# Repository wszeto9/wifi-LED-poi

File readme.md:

# WiFi-LED-Poi
USB-C Rechargable, WiFi Capable Glow Poi

<h2> Features:</h2>
<ul>
<li>ESP-32 MCU capable of WiFi-communication and syncronization of lights with music</li>
<li>Rechargable battery with a battery life of 3.5-5 hours</li>
<li>Programmable over USB-C</li>
<li>Charging over USB-C</li>
<li>0.47F Supercapacitor capable of nefarious discharge acts</li>
<li>Onboard accelerometer and microphone</li>
</ul>

PCB Bottom

PCB Top

PCBA

Glow Poi assembled with shell and battery

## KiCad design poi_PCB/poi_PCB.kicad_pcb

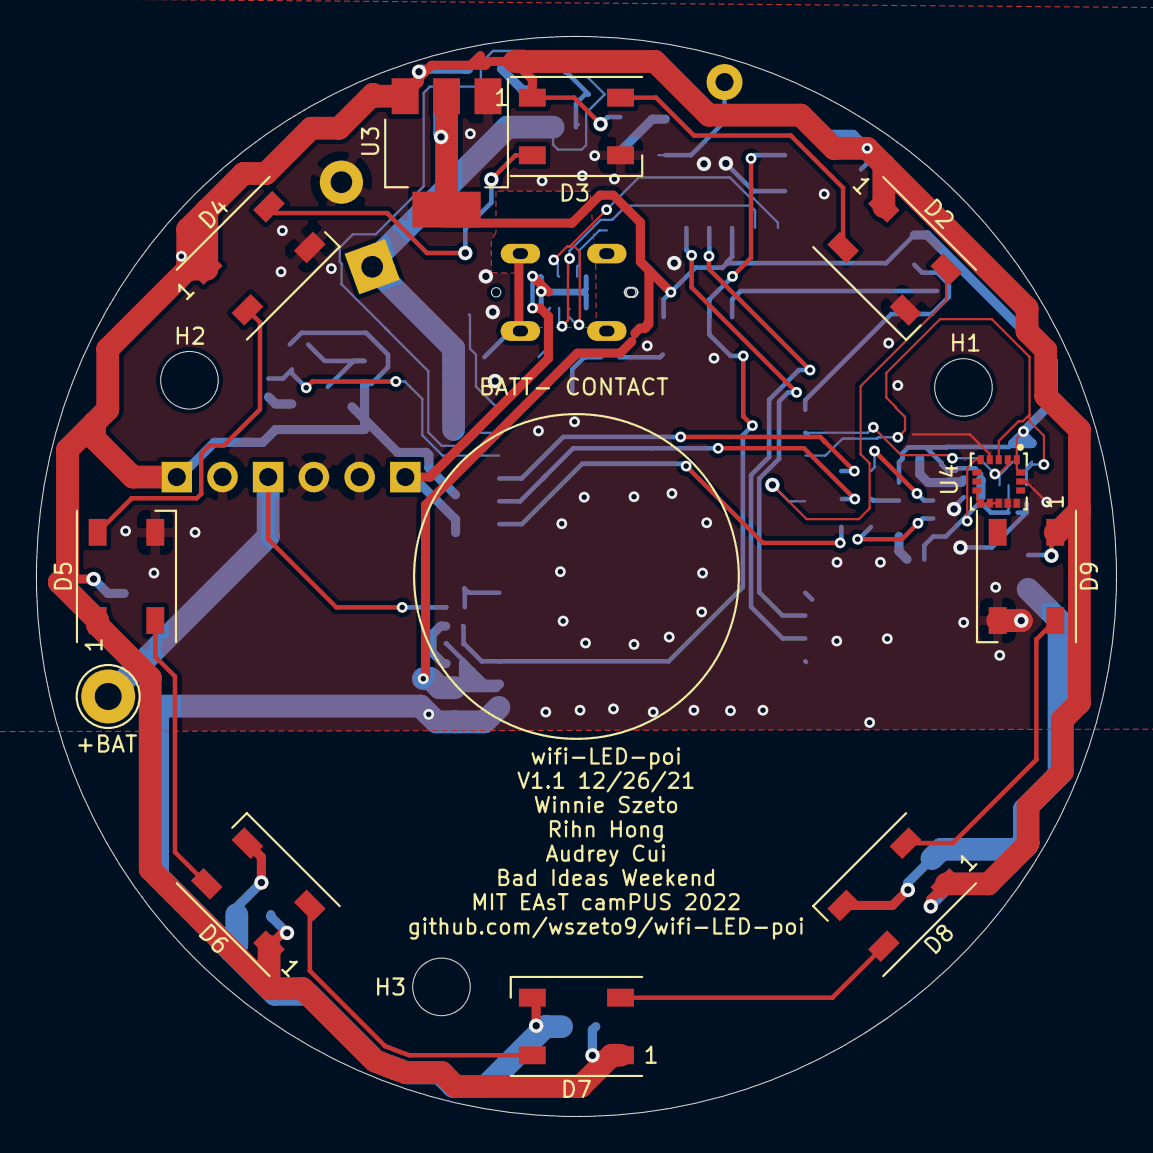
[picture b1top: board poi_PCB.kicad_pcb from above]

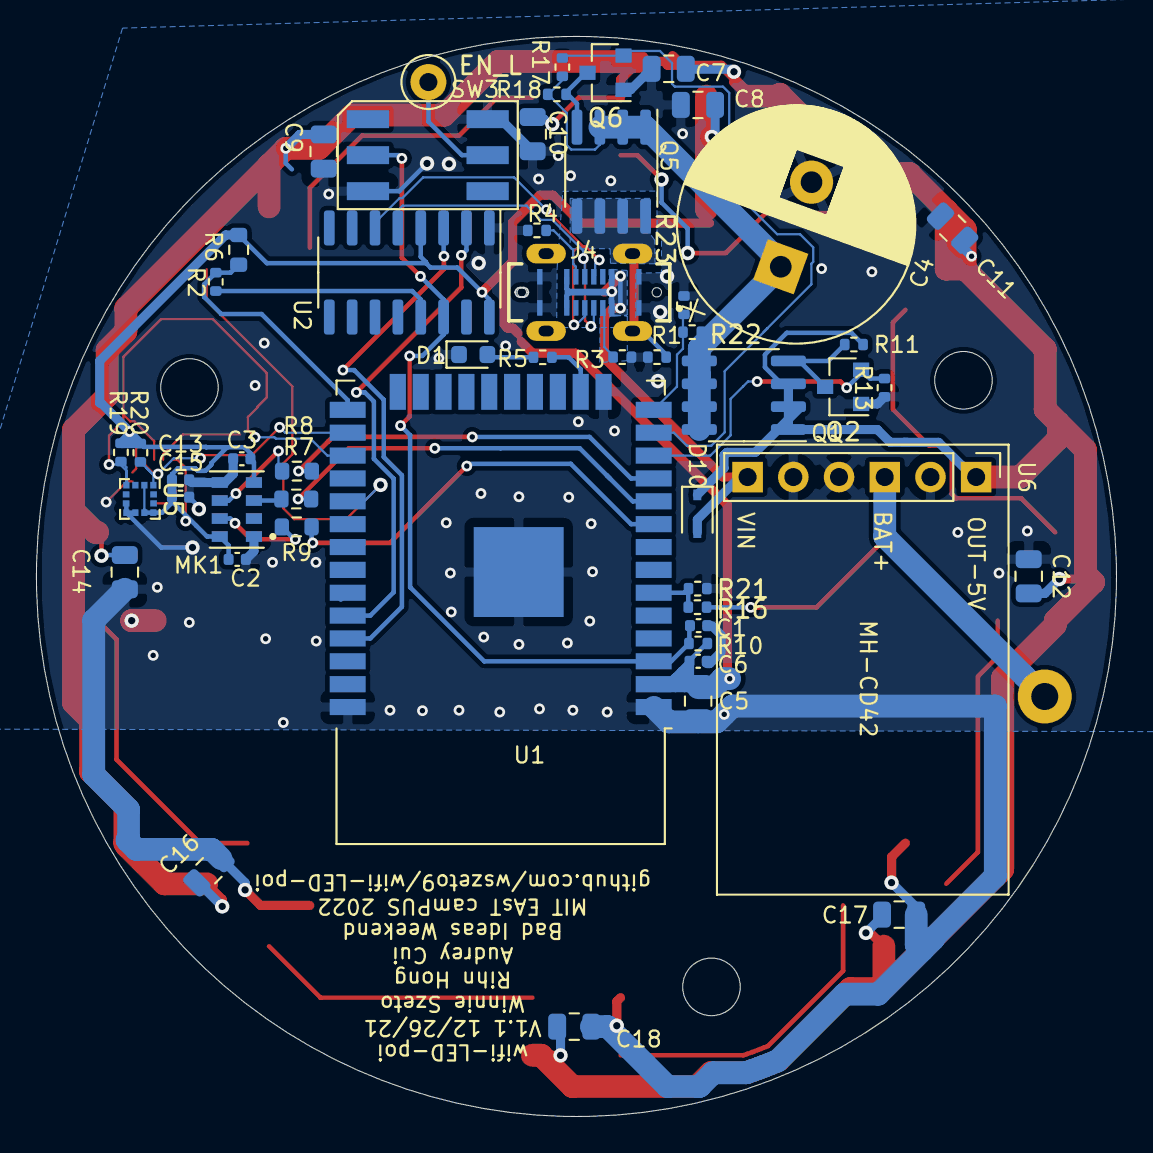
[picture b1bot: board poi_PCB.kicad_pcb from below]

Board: 2 copper layers, 60.0 x 60.0 mm, 66 parts (52 on the bottom side), 41 nets.

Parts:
+BAT: +BAT; TestPoint_THTPad_D3.0mm_Drill1.5mm
C1, C6: 100nF; C_0402_1005Metric
C2, C13, C15: .1uF; C_0402_1005Metric
C3: 220pF; C_0402_1005Metric
C4: 0.47F; CP_Radial_D13.0mm_P5.00mm
C5, C7, C8, C9, C10, C11, C12, C14, C16, C17, C18: 10uF; C_0805_2012Metric
D1: LED; LED_0603_1608Metric
D2, D3, D4, D5, D6, D7, D8, D9: WS2812B; LED_WS2812B_PLCC4_5.0x5.0mm_P3.2mm
D10: 1N5819WS; D_SOD-323
EN_L: 5V_EN_L; TestPoint_Loop_D1.80mm_Drill1.0mm_Beaded
H1, H2, H3: MountingHole; MountingHole_3.2mm_M3
J4: USB_C_Receptacle_USB2.0; GCT_USB4120-03-C_REVA
MK1: CMM-4030D-261-I2S-TR; MIC_CMM-4030D-261-I2S-TR
Q1, Q5: AO4407C; SOIC-8_3.9x4.9mm_P1.27mm
Q2, Q6: AO3400A; SOT-23
R1, R11, R13, R17, R18: 1K; R_0402_1005Metric
R2: 220; R_0402_1005Metric
R3, R4: 5.1K; R_0402_1005Metric
R5: 220R; R_0402_1005Metric
R6: 10K; R_0603_1608Metric
R7, R8, R9: 51R; R_0603_1608Metric
R10, R19, R20: 10K; R_0402_1005Metric
R16, R21, R22, R23: 100K; R_0402_1005Metric
SW3: TL2233OA
U1: ESP32-WROOM-32D; ESP32-WROOM-32
U2: CH340C; SOIC-16_3.9x9.9mm_P1.27mm
U3: AMS1117-3.3; SOT-223-3_TabPin2
U4: LSM6DS33TR; PQFN50P300X300X86-16N
U5: LIS2DH; LGA-12_2x2mm_P0.5mm
U6: MH-CD42

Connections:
+3V3: C2.1, C3.1, C5.1, C6.1, C8.1, C13.1, C15.1, MK1.4, MK1.8, R6.1, R10.2, R19.1, R20.1, U1.2, U2.4, U2.16, U3.2, U4.1, U4.5, U4.16, U5.2, U5.9, U5.10
+5V: C7.1, C9.1, C10.1, C11.1, C12.1, C14.1, C16.1, C17.1, C18.1, D2.1, D3.1, D4.1, D5.1, D6.1, D7.1, D8.1, D9.1, D10.1, Q1.1, Q1.2, Q1.3, R11.1, U3.3, U6.1
+BATT: +BAT.1, R16.1, U6.3
/5V_EN_L: EN_L.1, SW3.5
/BAT_VSENSE: R16.2, R21.1, U1.6
/BCLK: R8.2, U1.11
/CAP_VSENSE: R22.2, R23.1, U1.14
/CHARGE_CAP_EN: Q2.2, R13.2, U1.12
/D+: J4.A6, J4.B6, U2.5
/D-: J4.A7, J4.B7, U2.6
/D_OUT_I2S: R9.1, U1.9
/FIRE_L: Q6.2, R17.1, U1.13
/GPIO0: R2.1, R6.2, U1.25
/LED_SIG: D2.4, U1.29
/RST: C1.1, R10.1, SW3.2, U1.3, U2.14
/RXD: U1.35, U2.3
/SCL: R20.2, U1.26, U4.2, U5.1
/SDA: R19.2, U1.27, U4.3, U5.4
/SHIELD: J4.S1, Q5.5, Q5.6, Q5.7, Q5.8, R1.2
/TXD: U1.34, U2.2
/VBUS: D10.2, J4.A4, J4.A9, J4.B4, J4.B9, U6.6
/WS: R7.2, U1.10
GND: C1.2, C2.2, C3.2, C4.2, C5.2, C6.2, C7.2, C8.2, C9.2, C10.2, C11.2, C12.2, C13.2, C14.2, C15.2, C16.2, C17.2, C18.2, D1.1, D2.3, D3.3, D4.3, D5.3, D6.3, D7.3, D8.3, D9.3, J4.A1, J4.A12, J4.B1, J4.B12, MK1.1, MK1.5, Q2.1, Q6.1, R1.1, R3.1, R4.2, R13.1, R21.2, R23.2, SW3.3, SW3.4, U1.1, U1.15, U1.38, U1.39, U2.1, U3.1, U4.4, U4.8, U4.9, U4.10, U4.11, U4.12, U4.13, U4.15, U5.6, U5.7, U5.8, U6.2, U6.4, U6.5
unnamed: C4.1, Q1.5, Q1.6, Q1.7, Q1.8, Q5.1, Q5.2, Q5.3, R17.2, R18.1, R22.1
unnamed: D1.2, R5.1
unnamed: D2.2, D3.4
unnamed: D3.2, D4.4
unnamed: D4.2, D5.4
unnamed: D5.2, D6.4
unnamed: D6.2, D7.4
unnamed: D7.2, D8.4
unnamed: D8.2, D9.4
unnamed: J4.A5, R3.2
unnamed: J4.B5, R4.1
unnamed: MK1.3, R7.1
unnamed: MK1.6, R8.1
unnamed: MK1.7, R9.2
unnamed: Q1.4, Q2.3, R11.2
unnamed: Q5.4, Q6.3, R18.2
unnamed: R2.2, U2.13
unnamed: R5.2, U1.16

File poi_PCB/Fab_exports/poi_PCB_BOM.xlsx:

Comment | Designator | Footprint | LCSC
.1uF | C2,C13,C15 | Capacitor_SMD:C_0402_1005Metric | C1546
220pF | C3 | Capacitor_SMD:C_0402_1005Metric | C1530
0.47F | C4 | Capacitor_THT:CP_Radial_D13.0mm_P5.00mm | C239004
10uF | C5,C7,C8,C9,C10,C11,C12,C14,C16,C17,C18 | Capacitor_SMD:C_0805_2012Metric | C15850
100nF | C1,C6 | Capacitor_SMD:C_0402_1005Metric | C307331
LED | D1 | LED_SMD:LED_0603_1608Metric | C2290
1N5819WS | D10 | Diode_SMD:D_SOD-323 | C191023
LIS2DH | U5 | Package_LGA:LGA-12_2x2mm_P0.5mm | C110926
AO3400A | Q2,Q3,Q4,Q6,Q7,Q8 | Package_TO_SOT_SMD:SOT-23 | C20917
AO4407C | Q1,Q5 | Package_SO:SOIC-8_3.9x4.9mm_P1.27mm | C20897
1K | R1 | Resistor_SMD:R_0402_1005Metric | C25744
10K | R10,R11,R13,R17,R18,R19,R20 | Resistor_SMD:R_0402_1005Metric | C25744
10K | R6,R14,R15 | Resistor_SMD:R_0603_1608Metric | C25804
220 | R2 | Resistor_SMD:R_0402_1005Metric | C25091
100K | R16,R21,R22,R23 | Resistor_SMD:R_0402_1005Metric | C25741
5.1K | R3,R4 | Resistor_SMD:R_0402_1005Metric | C25905
220R | R5 | Resistor_SMD:R_0402_1005Metric | C25091
51R | R7,R8,R9 | Resistor_SMD:R_0603_1608Metric | C23197

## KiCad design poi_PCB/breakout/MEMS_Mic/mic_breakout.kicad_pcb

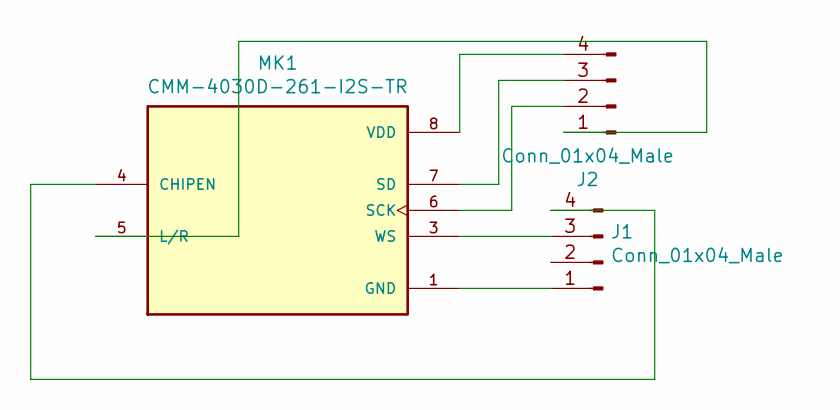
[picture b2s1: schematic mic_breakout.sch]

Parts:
J1, J2: Conn_01x04_Male; PinHeader_1x04_P2.54mm_Vertical
MK1: CMM-4030D-261-I2S-TR; MIC_CMM-4030D-261-I2S-TR; PARTREV 1.0

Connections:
unnamed: J1.1, MK1.1 (GND)
unnamed: J1.3, MK1.3 (WS)
unnamed: J1.4, MK1.4 (CHIPEN)
unnamed: J2.1, MK1.5 (L/R)
unnamed: J2.2, MK1.6 (SCK)
unnamed: J2.3, MK1.7 (SD)
unnamed: J2.4, MK1.8 (VDD)

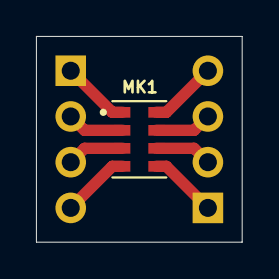
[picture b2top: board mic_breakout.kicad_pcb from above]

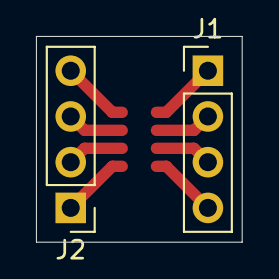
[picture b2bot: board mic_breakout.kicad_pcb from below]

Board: 2 copper layers, 11.4 x 11.4 mm, 3 parts (2 on the bottom side), 7 nets.

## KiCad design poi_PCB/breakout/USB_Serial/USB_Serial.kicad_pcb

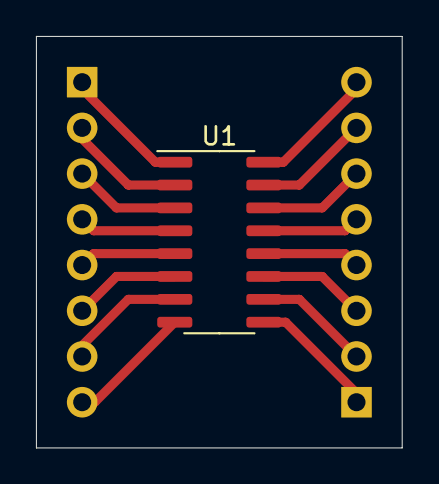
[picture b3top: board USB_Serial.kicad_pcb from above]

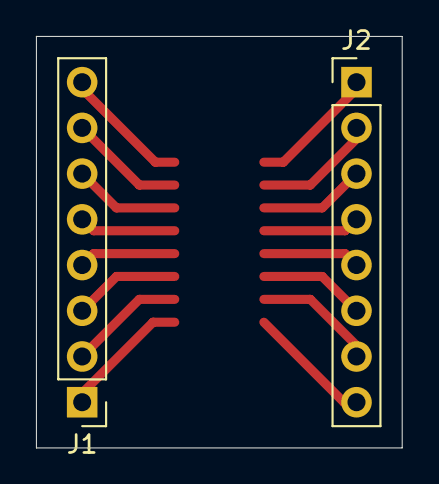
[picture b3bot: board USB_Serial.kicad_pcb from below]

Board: 2 copper layers, 20.3 x 22.9 mm, 3 parts (2 on the bottom side), 16 nets.

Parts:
J1, J2: Conn_01x08_Female; PinHeader_1x08_P2.54mm_Vertical
U1: CH340G; SOIC-16_3.9x9.9mm_P1.27mm

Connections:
unnamed: J1.1, U1.9
unnamed: J1.2, U1.10
unnamed: J1.3, U1.11
unnamed: J1.4, U1.12
unnamed: J1.5, U1.13
unnamed: J1.6, U1.14
unnamed: J1.7, U1.15
unnamed: J1.8, U1.16
unnamed: J2.1, U1.1
unnamed: J2.2, U1.2
unnamed: J2.3, U1.3
unnamed: J2.4, U1.4
unnamed: J2.5, U1.5
unnamed: J2.6, U1.6
unnamed: J2.7, U1.7
unnamed: J2.8, U1.8

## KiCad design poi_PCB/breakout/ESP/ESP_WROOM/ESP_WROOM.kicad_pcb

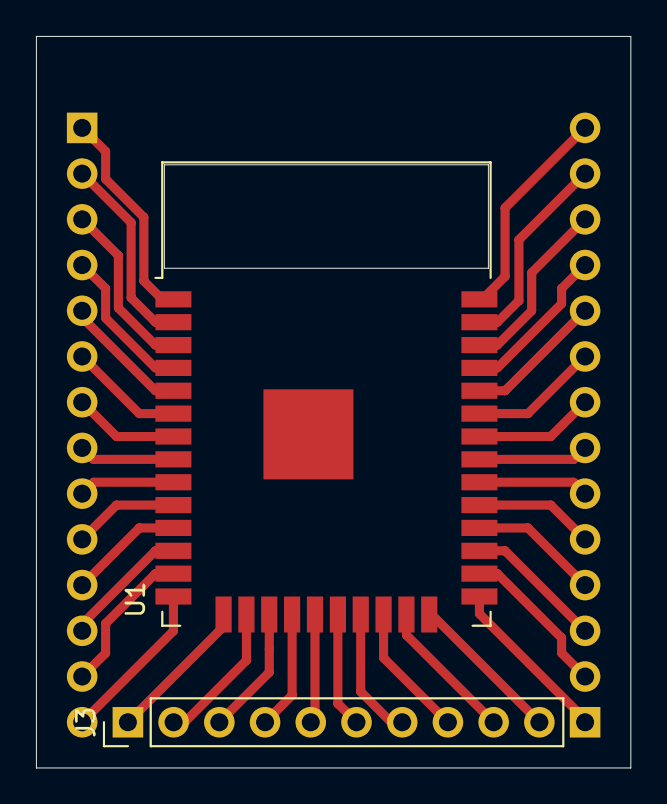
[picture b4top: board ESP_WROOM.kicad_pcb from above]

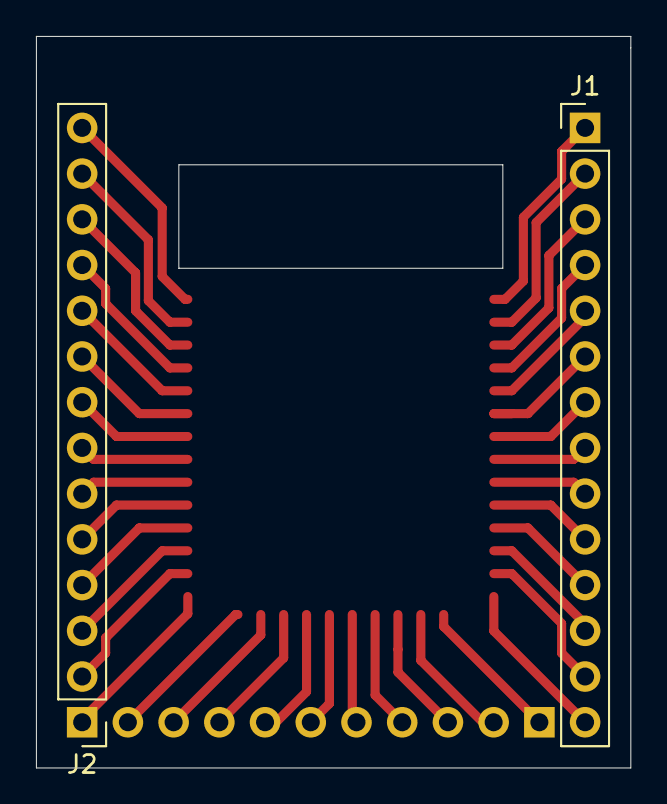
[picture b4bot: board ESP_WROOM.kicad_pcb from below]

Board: 2 copper layers, 33.0 x 40.6 mm, 4 parts (2 on the bottom side), 35 nets.

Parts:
J1, J2: Conn_01x14_Female; PinHeader_1x14_P2.54mm_Vertical
J3: Conn_01x10_Female; PinHeader_1x10_P2.54mm_Vertical
U1: ESP32-WROOM-32D; ESP32-WROOM-32

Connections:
/1: J1.1, J2.14, J3.1, U1.1, U1.15, U1.38, U1.39
/2: J1.2, U1.2
/3: J1.3, U1.3
/4: J1.4, U1.4
/5: J1.5, U1.5
/6: J1.6, U1.6
/7: J1.7, U1.7
/8: J1.8, U1.8
/9: J1.9, U1.9
/10: J1.10, U1.10
/11: J1.11, U1.11
/12: J1.12, U1.12
/13: J1.13, U1.13
/14: J1.14, U1.14
/16: J3.2, U1.16
/17: J3.3, U1.17
/18: J3.4, U1.18
/19: J3.5, U1.19
/20: J3.6, U1.20
/21: J3.7, U1.21
/22: J3.8, U1.22
/23: J3.9, U1.23
/24: J3.10, U1.24
/25: J2.1, U1.25
/26: J2.2, U1.26
/27: J2.3, U1.27
/28: J2.4, U1.28
/29: J2.5, U1.29
/30: J2.6, U1.30
/31: J2.7, U1.31
/33: J2.9, U1.33
/34: J2.10, U1.34
/35: J2.11, U1.35
/36: J2.12, U1.36
/37: J2.13, U1.37

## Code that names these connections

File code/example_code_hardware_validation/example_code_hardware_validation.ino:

void setup() {
  //pin declaration
  #define DEBUG_LED 13
  #define LED_PIN 17
  #define CAP_VSENSE 12
  #define CHARGE_CAP_EN 27
  #define BAT_VSENSE 34
  #define SCL 4
  #define SDA 16
  #define BCLK 26
  #define WS 25
  #define D_OUT_MIC 33
  #define FIRE_HIGH 14


  //pinMode
  pinMode(LED_PIN, OUTPUT);
  pinMode(CAP_VSENSE, INPUT);
  pinMode(CHARGE_CAP_EN, OUTPUT);
  pinMode(BAT_VSENSE, INPUT);
  pinMode(DEBUG_LED, OUTPUT);

  //IMU
  /*
  #include <Wire.h>
  #include <LSM6.h>
  LSM6 imu;
  char report[80];
  Wire.begin(SDA, SCL);
  imu.enableDefault();
  /* desired perameters: 
   *  1000 ODR_XL -high performance 1.66kHz
   *  01 FS_XL +/- 16g 
   *  00 BW_XL 400 Hz AA
   *  0b10000100 = 0x84
   *  
   
   imu.writeReg(0x10, 0x84); //sets accelerometer to +/- 16g
  */
  Serial.begin(9600);
}

void loop() {
  while(!Serial){}
  
  //Capacitor charging
  
  Serial.println(2*3.3*analogRead(CAP_VSENSE)/4095); //2:1 voltage divider, analogRead is out of 4095
  digitalWrite(CHARGE_CAP_EN, HIGH);
  delay(100);
  

  //IMU read
  /*
  imu.read();
  Serial.print("A[g] :");
  //.488 mg/LSB @ +/- 16g
  Serial.print((float)imu.a.x * .488/1000); 
  Serial.print(" ");
  Serial.print((float)imu.a.y * .488/1000); 
  Serial.print(" ");
  Serial.print((float)imu.a.z * .488/1000); 
  Serial.print(" ");
  Serial.print("G[dps] :");
  Serial.print((float)imu.g.x * 8.75/1000); 
  Serial.print(" ");
  Serial.print((float)imu.g.y * 8.75/1000); 
  Serial.print(" ");
  Serial.println((float)imu.g.z * 8.75/1000);
  */ 
}

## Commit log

2021-11-14 Initial upload
    Created schematic of board
2021-11-14 deleted unused files
2021-11-23 added TP4056 footprint
2021-11-25 Changed USB-> Serial chip, added documentation
    -CH340G replaced with CH340C to eliminate the need for a crystal
    -Part sourcing updated in BOM
    -minor edits based on available parts
    -Schematic updated to reflect changes
2021-11-25 PCB changed to white solder mask, added STEP files
2021-11-25 Added full assembly renders
    Checked to see how LEDs would diffuse with a battery in the center
2021-11-26 Added mounting holes
2021-12-01 Verified reset circuit
    Breadboarded and edited reset circuit.
    -USBC port moved closer to center
    -transistors replaced because of issues with transistor quality
2021-12-03 added code and calculations for accelerometer
2021-12-04 redone traces, changed accelerometer, supercapacitor and mic
2021-12-05 Verified pinouts
    -Pinouts all checked to be compatible with peripherals.
    -FIRE is pulled up to +CAP, and drains within 20 minutes if the device is turned off
2021-12-05 updated sourcing info
2021-12-06 Updated pictures and schematics, added analog RGB header
    analog RGB header is designed for 12V analog RGB strips
2021-12-06 Added fabrication files
2021-12-11 added manufacturing files
2021-12-25 Added validation code
2021-12-25 Update LSM6_serial.ino
    Changed pinout of LSM6 to reflect PCB
2021-12-25 Added mechanical assembly files
2021-12-26 Changed schematic based on testing
    -LED logic level shifter omitted due to slow switching speed of AO3400A
    -LED input moved to GPIO5 to avoid pulling up GPIO2 during UART programming
    -Gate pullup/pulldown resistors changed to 1K to allow for faster switching
    -analog RGB header omitted
2021-12-26 Added FastLED library via PlatformIO
    Switching programming platform to PlatformIO because FastLED does not work in the Arduino IDE.
2021-12-26 added microphone test code
    changes LED brightness based on volume
2021-12-27 added WLED source code
2021-12-27 Added mold specific files
2021-12-27 reorganized file folders
2022-01-02 added example code
    blinks LED, speed varies with acceleration data measured. faster acceleration leads to faster blinks
2022-01-02 Updated 3D files
2022-01-02 included tolerances in parts
2022-01-03 updated assembly video to reflect recent edits
2022-01-03 added tolerances to mold
2022-01-03 changed height of hole to reflect bridging tolerances in 3d printing
2022-01-03 edited tolerances
2022-01-03 Update poi_PCB.sch-bak
2022-01-03 added images of product
2022-01-15 add music to color translation code
2022-01-15 pump up brightness
2022-01-16 turns red when plugged in
2022-01-17 Added accelerometer
    -Added accelerometer code to vary brightness based on accel
    -LED indicator at the bottom changes PWM cycle based on battery charge
2022-01-20 added charge/discharge
2022-07-10 updated gitignore
2023-01-29 edited gitignore
